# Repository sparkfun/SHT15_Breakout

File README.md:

**NOTE:** *This product has been retired from our catalog. If you are looking for more up-to-date info, please check out some of these resources to see how other users are still hacking and improving on this product.*
* *[SparkFun Forum](https://forum.sparkfun.com/)*
* *[Comments Here on GitHub](https://github.com/sparkfun/SHT15_Breakout/issues)*
* *[IRC Channel](https://www.sparkfun.com/news/263)*

SHT15 Breakout
==============
[  
*SHT15 Breakout Board (SEN-13683)*](https://www.sparkfun.com/products/13683)

Repository Contents
-------------------
* **/Hardware** - All Eagle design files (.brd, .sch)
* **/Libraries** - Contains the Arduino library and examples for the sensor
* **/Production** - Test bed files and production panel files

Documentation
--------------
* **[Installing an Arduino Library Guide](https://learn.sparkfun.com/tutorials/installing-an-arduino-library)** - Basic information on how to install an Arduino library.
* **[Hookup Guide](https://learn.sparkfun.com/tutorials/sht15-humidity-and-temperature-sensor-hookup-guide)** - Basic hookup guide for the sensor.
* **[SparkFun Fritzing repo](https://github.com/sparkfun/Fritzing_Parts)** - Fritzing diagrams for SparkFun products.
* **[SparkFun 3D Model repo](https://github.com/sparkfun/3D_Models)** - 3D models of SparkFun products. 

License Information
-------------------
This product is _**open source**_! 

The **hardware** is released under [Creative Commons ShareAlike 4.0 International](https://creativecommons.org/licenses/by-sa/4.0/).

The **code** is beerware; if you see me (or any other SparkFun employee) at the local, and you've found our code helpful, please buy us a round!

Please use, reuse, and modify these files as you see fit. Please maintain attribution to SparkFun Electronics and release anything derivative under the same license.

Distributed as-is; no warranty is given.

- Your friends at SparkFun.

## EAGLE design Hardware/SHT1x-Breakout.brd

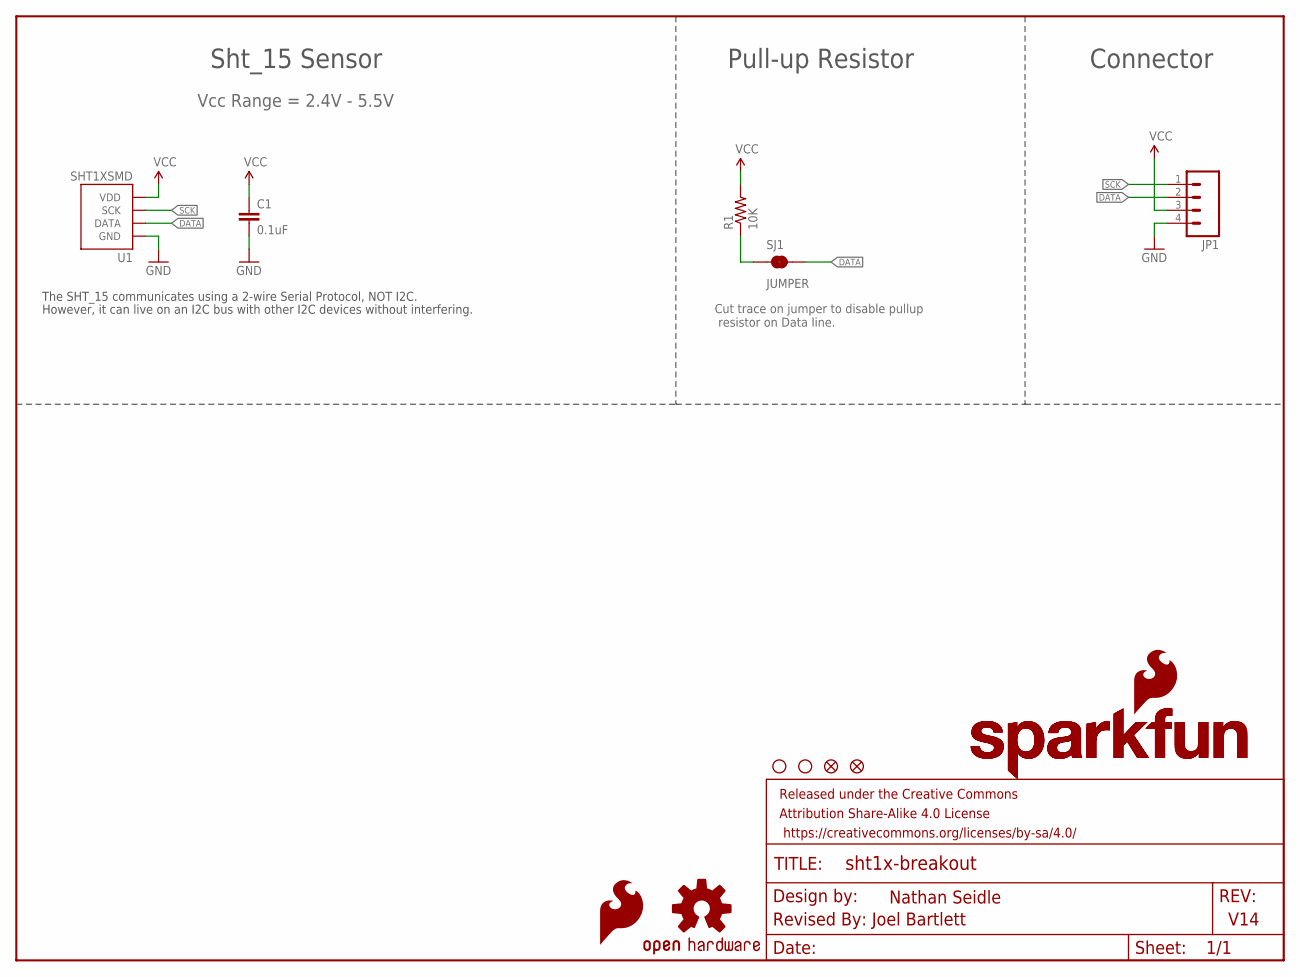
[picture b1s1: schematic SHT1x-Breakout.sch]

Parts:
C1: 0.1uF; 0603-CAP
FID1, FID2: FIDUCIAL1X2; FIDUCIAL-1X2
FRAME1: FRAME-LETTER; CREATIVE_COMMONS
JP1: M04PTH; 1X04
LOGO1: OSHW-LOGOS; OSHW-LOGO-S
LOGO2: SFE_LOGO_NAME.1_INCH; SFE_LOGO_NAME_.1
LOGO4: SFE_LOGO_FLAME.1_INCH; SFE_LOGO_FLAME_.1
LOGO5: SFE_LOGO_NAME_FLAME.1_INCH; SFE_LOGO_NAME_FLAME_.1
R1: 10K; 0603-RES
SJ1: JUMPER; PAD-JUMPER-2-NC_BY_TRACE_YES_SILK
STANDOFF1, STANDOFF2: STAND-OFF
U1: SHT1XSMD; SHT1X

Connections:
DATA: JP1.2, SJ1.2, U1.2 (DATA)
GND: C1.2, JP1.4, U1.1 (GND)
unnamed: R1.1, SJ1.1
SCK: JP1.1, U1.3 (SCK)
VCC: C1.1, JP1.3, R1.2, U1.4 (VDD)

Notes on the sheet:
Sht_15 Sensor
The SHT_15 communicates using a 2-wire Serial Protocol, NOT I2C.
However, it can live on an I2C bus with other I2C devices without interfering.
Connector
Pull-up Resistor
Nathan Seidle
V14
Revised By: Joel Bartlett
Vcc Range = 2.4V - 5.5V
Cut trace on jumper to disable pullup resistor on Data line.

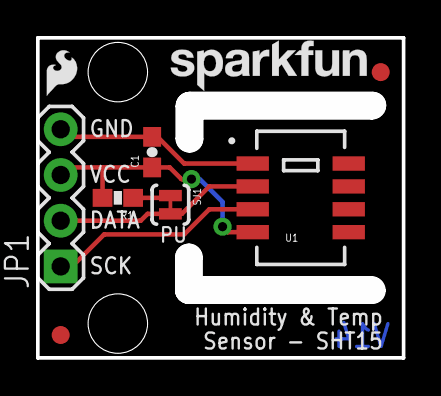
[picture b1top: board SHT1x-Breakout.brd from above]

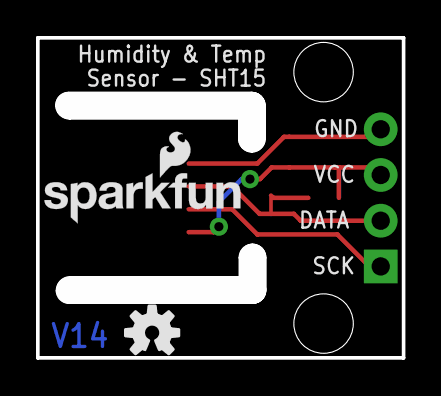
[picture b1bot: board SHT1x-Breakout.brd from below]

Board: 2 copper layers, 19.0 x 16.5 mm, 14 parts (2 on the bottom side), 5 nets.

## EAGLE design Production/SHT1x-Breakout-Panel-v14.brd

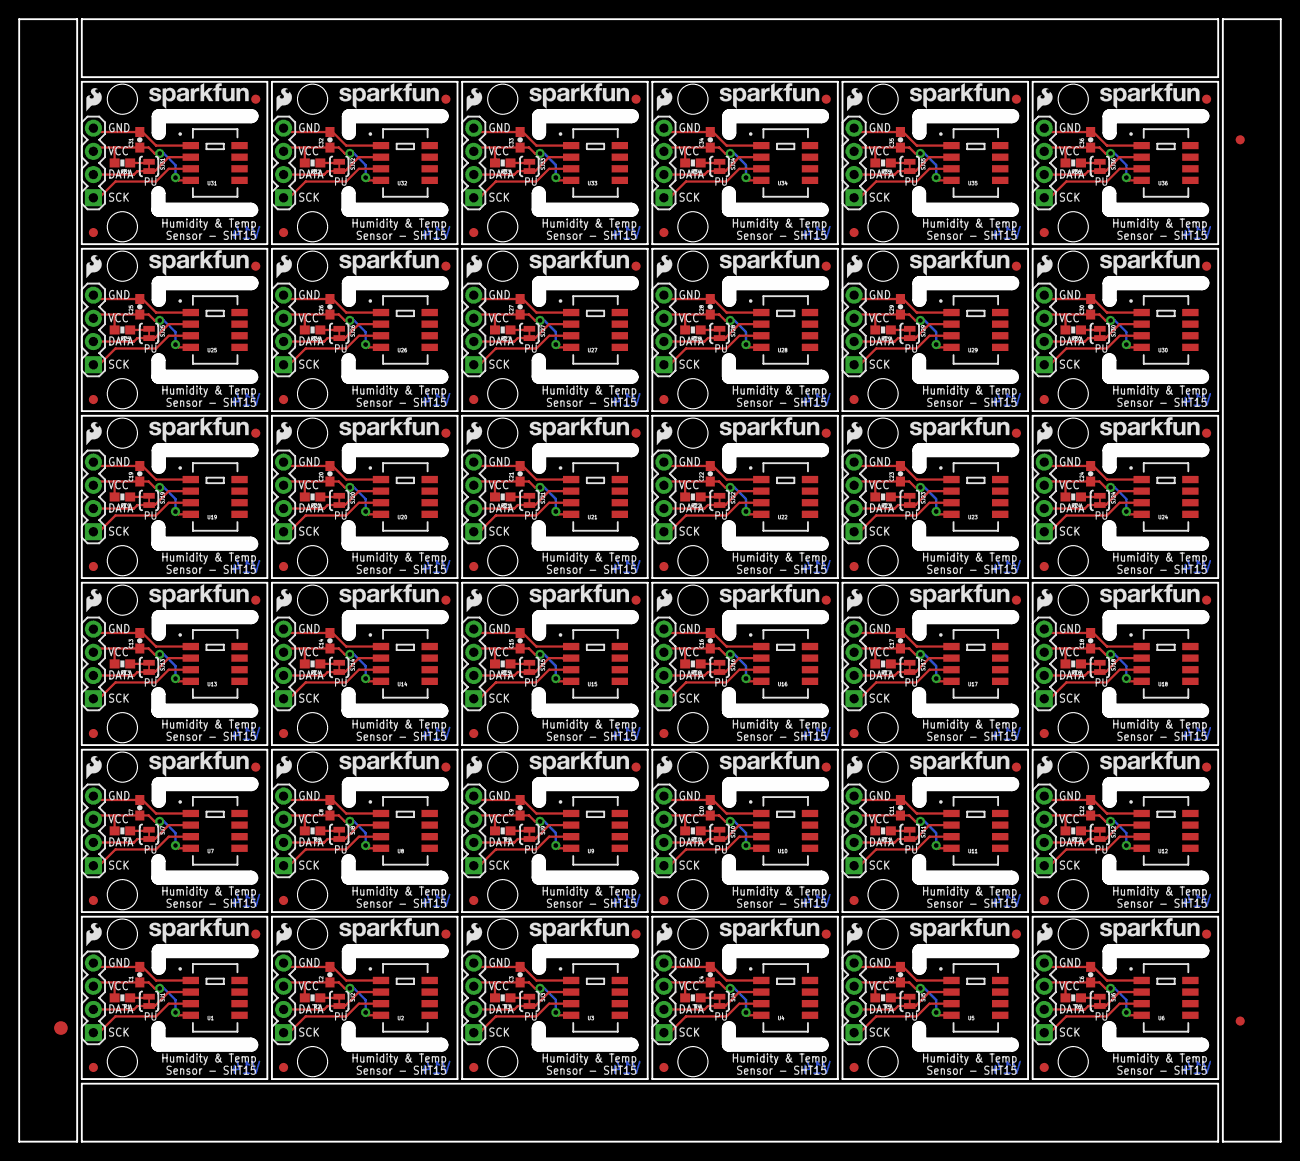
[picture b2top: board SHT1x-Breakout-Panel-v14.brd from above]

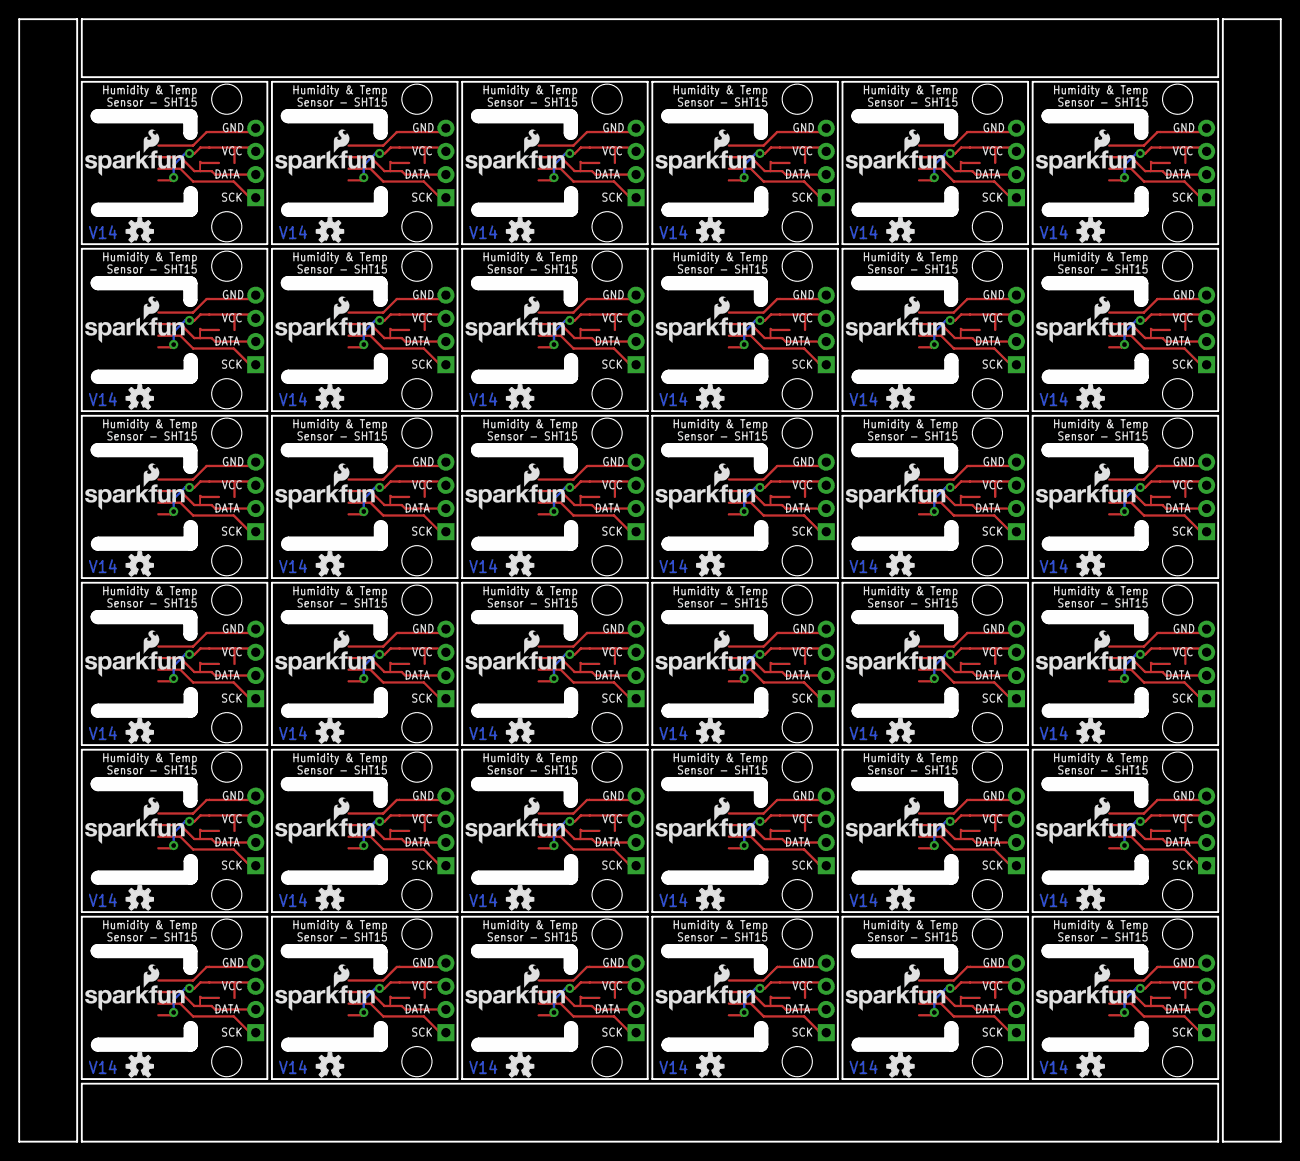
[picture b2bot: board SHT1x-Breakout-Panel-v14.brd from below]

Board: 2 copper layers, 136.9 x 121.6 mm, 471 parts (72 on the bottom side), 180 nets.

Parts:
C1, C2, C3, C4, C5, C6, C7, C8, C9, C10, C11, C12, C13, C14, C15, C16, C17, C18, C19, C20, C21, C22, C23, C24, C25, C26, C27, C28, C29, C30, C31, C32, C33, C34, C35, C36: 0.1uF; 0603-CAP
E$1: FIDUCIAL-1.5X3
E$4, E$5: FIDUCIAL-1X2
FID1, FID2, FID3, FID4, FID5, FID6, FID7, FID8, FID9, FID10, FID11, FID12, FID13, FID14, FID15, FID16, FID17, FID18, FID19, FID20, FID21, FID22, FID23, FID24, FID25, FID26, FID27, FID28, FID29, FID30, FID31, FID32, FID33, FID34, FID35, FID36, FID37, FID38, FID39, FID40, FID41, FID42, FID43, FID44, FID45, FID46, FID47, FID48, FID49, FID50, FID51, FID52, FID53, FID54, FID55, FID56, FID57, FID58, FID59, FID60, FID61, FID62, FID63, FID64, FID65, FID66, FID67, FID68, FID69, FID70, FID71, FID72: FIDUCIAL1X2; FIDUCIAL-1X2
JP1, JP2, JP3, JP4, JP5, JP6, JP7, JP8, JP9, JP10, JP11, JP12, JP13, JP14, JP15, JP16, JP17, JP18, JP19, JP20, JP21, JP22, JP23, JP24, JP25, JP26, JP27, JP28, JP29, JP30, JP31, JP32, JP33, JP34, JP35, JP36: 1X04
LOGO1, LOGO3, LOGO9, LOGO13, LOGO17, LOGO21, LOGO25, LOGO29, LOGO33, LOGO37, LOGO41, LOGO45, LOGO49, LOGO53, LOGO57, LOGO61, LOGO65, LOGO69, LOGO73, LOGO77, LOGO81, LOGO85, LOGO89, LOGO93, LOGO97, LOGO101, LOGO105, LOGO109, LOGO113, LOGO117, LOGO121, LOGO125, LOGO129, LOGO133, LOGO137, LOGO141: OSHW-LOGOS; OSHW-LOGO-S
LOGO2, LOGO7, LOGO11, LOGO15, LOGO19, LOGO23, LOGO27, LOGO31, LOGO35, LOGO39, LOGO43, LOGO47, LOGO51, LOGO55, LOGO59, LOGO63, LOGO67, LOGO71, LOGO75, LOGO79, LOGO83, LOGO87, LOGO91, LOGO95, LOGO99, LOGO103, LOGO107, LOGO111, LOGO115, LOGO119, LOGO123, LOGO127, LOGO131, LOGO135, LOGO139, LOGO143: SFE_LOGO_NAME.1_INCH; SFE_LOGO_NAME_.1
LOGO4, LOGO6, LOGO10, LOGO14, LOGO18, LOGO22, LOGO26, LOGO30, LOGO34, LOGO38, LOGO42, LOGO46, LOGO50, LOGO54, LOGO58, LOGO62, LOGO66, LOGO70, LOGO74, LOGO78, LOGO82, LOGO86, LOGO90, LOGO94, LOGO98, LOGO102, LOGO106, LOGO110, LOGO114, LOGO118, LOGO122, LOGO126, LOGO130, LOGO134, LOGO138, LOGO142: SFE_LOGO_FLAME.1_INCH; SFE_LOGO_FLAME_.1
LOGO5, LOGO8, LOGO12, LOGO16, LOGO20, LOGO24, LOGO28, LOGO32, LOGO36, LOGO40, LOGO44, LOGO48, LOGO52, LOGO56, LOGO60, LOGO64, LOGO68, LOGO72, LOGO76, LOGO80, LOGO84, LOGO88, LOGO92, LOGO96, LOGO100, LOGO104, LOGO108, LOGO112, LOGO116, LOGO120, LOGO124, LOGO128, LOGO132, LOGO136, LOGO140, LOGO144: SFE_LOGO_NAME_FLAME.1_INCH; SFE_LOGO_NAME_FLAME_.1
R1, R2, R3, R4, R5, R6, R7, R8, R9, R10, R11, R12, R13, R14, R15, R16, R17, R18, R19, R20, R21, R22, R23, R24, R25, R26, R27, R28, R29, R30, R31, R32, R33, R34, R35, R36: 10K; 0603-RES
SJ1, SJ2, SJ3, SJ4, SJ5, SJ6, SJ7, SJ8, SJ9, SJ10, SJ11, SJ12, SJ13, SJ14, SJ15, SJ16, SJ17, SJ18, SJ19, SJ20, SJ21, SJ22, SJ23, SJ24, SJ25, SJ26, SJ27, SJ28, SJ29, SJ30, SJ31, SJ32, SJ33, SJ34, SJ35, SJ36: JUMPER; PAD-JUMPER-2-NC_BY_TRACE_YES_SILK
STANDOFF1, STANDOFF2, STANDOFF3, STANDOFF4, STANDOFF5, STANDOFF6, STANDOFF7, STANDOFF8, STANDOFF9, STANDOFF10, STANDOFF11, STANDOFF12, STANDOFF13, STANDOFF14, STANDOFF15, STANDOFF16, STANDOFF17, STANDOFF18, STANDOFF19, STANDOFF20, STANDOFF21, STANDOFF22, STANDOFF23, STANDOFF24, STANDOFF25, STANDOFF26, STANDOFF27, STANDOFF28, STANDOFF29, STANDOFF30, STANDOFF31, STANDOFF32, STANDOFF33, STANDOFF34, STANDOFF35, STANDOFF36, STANDOFF37, STANDOFF38, STANDOFF39, STANDOFF40, STANDOFF41, STANDOFF42, STANDOFF43, STANDOFF44, STANDOFF45, STANDOFF46, STANDOFF47, STANDOFF48, STANDOFF49, STANDOFF50, STANDOFF51, STANDOFF52, STANDOFF53, STANDOFF54, STANDOFF55, STANDOFF56, STANDOFF57, STANDOFF58, STANDOFF59, STANDOFF60, STANDOFF61, STANDOFF62, STANDOFF63, STANDOFF64, STANDOFF65, STANDOFF66, STANDOFF67, STANDOFF68, STANDOFF69, STANDOFF70, STANDOFF71, STANDOFF72: STAND-OFF
U1, U2, U3, U4, U5, U6, U7, U8, U9, U10, U11, U12, U13, U14, U15, U16, U17, U18, U19, U20, U21, U22, U23, U24, U25, U26, U27, U28, U29, U30, U31, U32, U33, U34, U35, U36: SHT1XSMD; SHT1X

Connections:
DATA: JP1.2, SJ1.2, U1.2
DATA1: JP2.2, SJ2.2, U2.2
DATA2: JP3.2, SJ3.2, U3.2
DATA3: JP4.2, SJ4.2, U4.2
DATA4: JP5.2, SJ5.2, U5.2
DATA5: JP6.2, SJ6.2, U6.2
DATA6: JP7.2, SJ7.2, U7.2
DATA7: JP8.2, SJ8.2, U8.2
DATA8: JP9.2, SJ9.2, U9.2
DATA9: JP10.2, SJ10.2, U10.2
DATA10: JP11.2, SJ11.2, U11.2
DATA11: JP12.2, SJ12.2, U12.2
DATA12: JP13.2, SJ13.2, U13.2
DATA13: JP14.2, SJ14.2, U14.2
DATA14: JP15.2, SJ15.2, U15.2
DATA15: JP16.2, SJ16.2, U16.2
DATA16: JP17.2, SJ17.2, U17.2
DATA17: JP18.2, SJ18.2, U18.2
DATA18: JP19.2, SJ19.2, U19.2
DATA19: JP20.2, SJ20.2, U20.2
DATA20: JP21.2, SJ21.2, U21.2
DATA21: JP22.2, SJ22.2, U22.2
DATA22: JP23.2, SJ23.2, U23.2
DATA23: JP24.2, SJ24.2, U24.2
DATA24: JP25.2, SJ25.2, U25.2
DATA25: JP26.2, SJ26.2, U26.2
DATA26: JP27.2, SJ27.2, U27.2
DATA27: JP28.2, SJ28.2, U28.2
DATA28: JP29.2, SJ29.2, U29.2
DATA29: JP30.2, SJ30.2, U30.2
DATA30: JP31.2, SJ31.2, U31.2
DATA31: JP32.2, SJ32.2, U32.2
DATA32: JP33.2, SJ33.2, U33.2
DATA33: JP34.2, SJ34.2, U34.2
DATA34: JP35.2, SJ35.2, U35.2
DATA35: JP36.2, SJ36.2, U36.2
GND: C1.2, JP1.4, U1.1
GND1: C2.2, JP2.4, U2.1
GND2: C3.2, JP3.4, U3.1
GND3: C4.2, JP4.4, U4.1
GND4: C5.2, JP5.4, U5.1
GND5: C6.2, JP6.4, U6.1
GND6: C7.2, JP7.4, U7.1
GND7: C8.2, JP8.4, U8.1
GND8: C9.2, JP9.4, U9.1
GND9: C10.2, JP10.4, U10.1
GND10: C11.2, JP11.4, U11.1
GND11: C12.2, JP12.4, U12.1
GND12: C13.2, JP13.4, U13.1
GND13: C14.2, JP14.4, U14.1
GND14: C15.2, JP15.4, U15.1
GND15: C16.2, JP16.4, U16.1
GND16: C17.2, JP17.4, U17.1
GND17: C18.2, JP18.4, U18.1
GND18: C19.2, JP19.4, U19.1
GND19: C20.2, JP20.4, U20.1
GND20: C21.2, JP21.4, U21.1
GND21: C22.2, JP22.4, U22.1
GND22: C23.2, JP23.4, U23.1
GND23: C24.2, JP24.4, U24.1
GND24: C25.2, JP25.4, U25.1
GND25: C26.2, JP26.4, U26.1
GND26: C27.2, JP27.4, U27.1
GND27: C28.2, JP28.4, U28.1
GND28: C29.2, JP29.4, U29.1
GND29: C30.2, JP30.4, U30.1
GND30: C31.2, JP31.4, U31.1
GND31: C32.2, JP32.4, U32.1
GND32: C33.2, JP33.4, U33.1
GND33: C34.2, JP34.4, U34.1
GND34: C35.2, JP35.4, U35.1
GND35: C36.2, JP36.4, U36.1
unnamed: R1.1, SJ1.1
unnamed: R2.1, SJ2.1
unnamed: R3.1, SJ3.1
unnamed: R4.1, SJ4.1
unnamed: R5.1, SJ5.1
unnamed: R6.1, SJ6.1
unnamed: R7.1, SJ7.1
unnamed: R8.1, SJ8.1
unnamed: R9.1, SJ9.1
unnamed: R10.1, SJ10.1
unnamed: R11.1, SJ11.1
unnamed: R12.1, SJ12.1
unnamed: R13.1, SJ13.1
unnamed: R14.1, SJ14.1
unnamed: R15.1, SJ15.1
unnamed: R16.1, SJ16.1
unnamed: R17.1, SJ17.1
unnamed: R18.1, SJ18.1
unnamed: R19.1, SJ19.1
unnamed: R20.1, SJ20.1
unnamed: R21.1, SJ21.1
unnamed: R22.1, SJ22.1
unnamed: R23.1, SJ23.1
unnamed: R24.1, SJ24.1
unnamed: R25.1, SJ25.1
unnamed: R26.1, SJ26.1
unnamed: R27.1, SJ27.1
unnamed: R28.1, SJ28.1
unnamed: R29.1, SJ29.1
unnamed: R30.1, SJ30.1
unnamed: R31.1, SJ31.1
unnamed: R32.1, SJ32.1
unnamed: R33.1, SJ33.1
unnamed: R34.1, SJ34.1
unnamed: R35.1, SJ35.1
unnamed: R36.1, SJ36.1
SCK: JP1.1, U1.3
SCK1: JP2.1, U2.3
SCK2: JP3.1, U3.3
SCK3: JP4.1, U4.3
SCK4: JP5.1, U5.3
SCK5: JP6.1, U6.3
SCK6: JP7.1, U7.3
SCK7: JP8.1, U8.3
SCK8: JP9.1, U9.3
SCK9: JP10.1, U10.3
SCK10: JP11.1, U11.3
SCK11: JP12.1, U12.3
SCK12: JP13.1, U13.3
SCK13: JP14.1, U14.3
SCK14: JP15.1, U15.3
SCK15: JP16.1, U16.3
SCK16: JP17.1, U17.3
SCK17: JP18.1, U18.3
SCK18: JP19.1, U19.3
SCK19: JP20.1, U20.3
SCK20: JP21.1, U21.3
SCK21: JP22.1, U22.3
SCK22: JP23.1, U23.3
SCK23: JP24.1, U24.3
SCK24: JP25.1, U25.3
SCK25: JP26.1, U26.3
SCK26: JP27.1, U27.3
SCK27: JP28.1, U28.3
SCK28: JP29.1, U29.3
SCK29: JP30.1, U30.3
SCK30: JP31.1, U31.3
SCK31: JP32.1, U32.3
SCK32: JP33.1, U33.3
SCK33: JP34.1, U34.3
SCK34: JP35.1, U35.3
SCK35: JP36.1, U36.3
VCC: C1.1, JP1.3, R1.2, U1.4
VCC1: C2.1, JP2.3, R2.2, U2.4
VCC2: C3.1, JP3.3, R3.2, U3.4
VCC3: C4.1, JP4.3, R4.2, U4.4
VCC4: C5.1, JP5.3, R5.2, U5.4
VCC5: C6.1, JP6.3, R6.2, U6.4
VCC6: C7.1, JP7.3, R7.2, U7.4
VCC7: C8.1, JP8.3, R8.2, U8.4
VCC8: C9.1, JP9.3, R9.2, U9.4
VCC9: C10.1, JP10.3, R10.2, U10.4
VCC10: C11.1, JP11.3, R11.2, U11.4
VCC11: C12.1, JP12.3, R12.2, U12.4
VCC12: C13.1, JP13.3, R13.2, U13.4
VCC13: C14.1, JP14.3, R14.2, U14.4
VCC14: C15.1, JP15.3, R15.2, U15.4
VCC15: C16.1, JP16.3, R16.2, U16.4
VCC16: C17.1, JP17.3, R17.2, U17.4
VCC17: C18.1, JP18.3, R18.2, U18.4
VCC18: C19.1, JP19.3, R19.2, U19.4
VCC19: C20.1, JP20.3, R20.2, U20.4
VCC20: C21.1, JP21.3, R21.2, U21.4
VCC21: C22.1, JP22.3, R22.2, U22.4
VCC22: C23.1, JP23.3, R23.2, U23.4
VCC23: C24.1, JP24.3, R24.2, U24.4
VCC24: C25.1, JP25.3, R25.2, U25.4
VCC25: C26.1, JP26.3, R26.2, U26.4
VCC26: C27.1, JP27.3, R27.2, U27.4
VCC27: C28.1, JP28.3, R28.2, U28.4
VCC28: C29.1, JP29.3, R29.2, U29.4
VCC29: C30.1, JP30.3, R30.2, U30.4
VCC30: C31.1, JP31.3, R31.2, U31.4
VCC31: C32.1, JP32.3, R32.2, U32.4
VCC32: C33.1, JP33.3, R33.2, U33.4
VCC33: C34.1, JP34.3, R34.2, U34.4
VCC34: C35.1, JP35.3, R35.2, U35.4
VCC35: C36.1, JP36.3, R36.2, U36.4

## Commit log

2013-09-03 Initial file commit
2015-03-30 Initial Revision Commit
    Testing to make sure changes only happen to V_1.4 branch. Initial
    layout of new revision.
2015-04-01 Initial Layout finished
    Initial Layout finished - ready for monday review
2015-04-06 Monday Review Complete
    Monday Review Changes implemented. Bottom silk on pins, names and
    version numbers, + a few minor fixes.
2015-05-08 Ready for final QC approval before protos
    Addressed QC issues. Minor route changes. Added PROD_ID to SHT_15.
    Altered silk name to match website name.
2015-07-13 Moved silk to avoid fiducial
    Moved silk to avoid fiducial
2015-07-14 Moved Route out note to Dimension layer
    Moved Route out note to Dimension layer
2015-07-15 created panel v14
2015-09-16 Adding Library and updated ReadMe
    Adding Library and updated ReadMe
2015-09-21 Updated names for library files.

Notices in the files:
parts and their libraries:
SparkFun-Sensors: Licensing: Creative Commons ShareAlike 4.0 International - https://creativecommons.org/licenses/by-sa/4.0
SparkFun-Aesthetics: Released under the Creative Commons Attribution Share-Alike 4.0 License
SparkFun-Aesthetics: Released under the Creative Commons
